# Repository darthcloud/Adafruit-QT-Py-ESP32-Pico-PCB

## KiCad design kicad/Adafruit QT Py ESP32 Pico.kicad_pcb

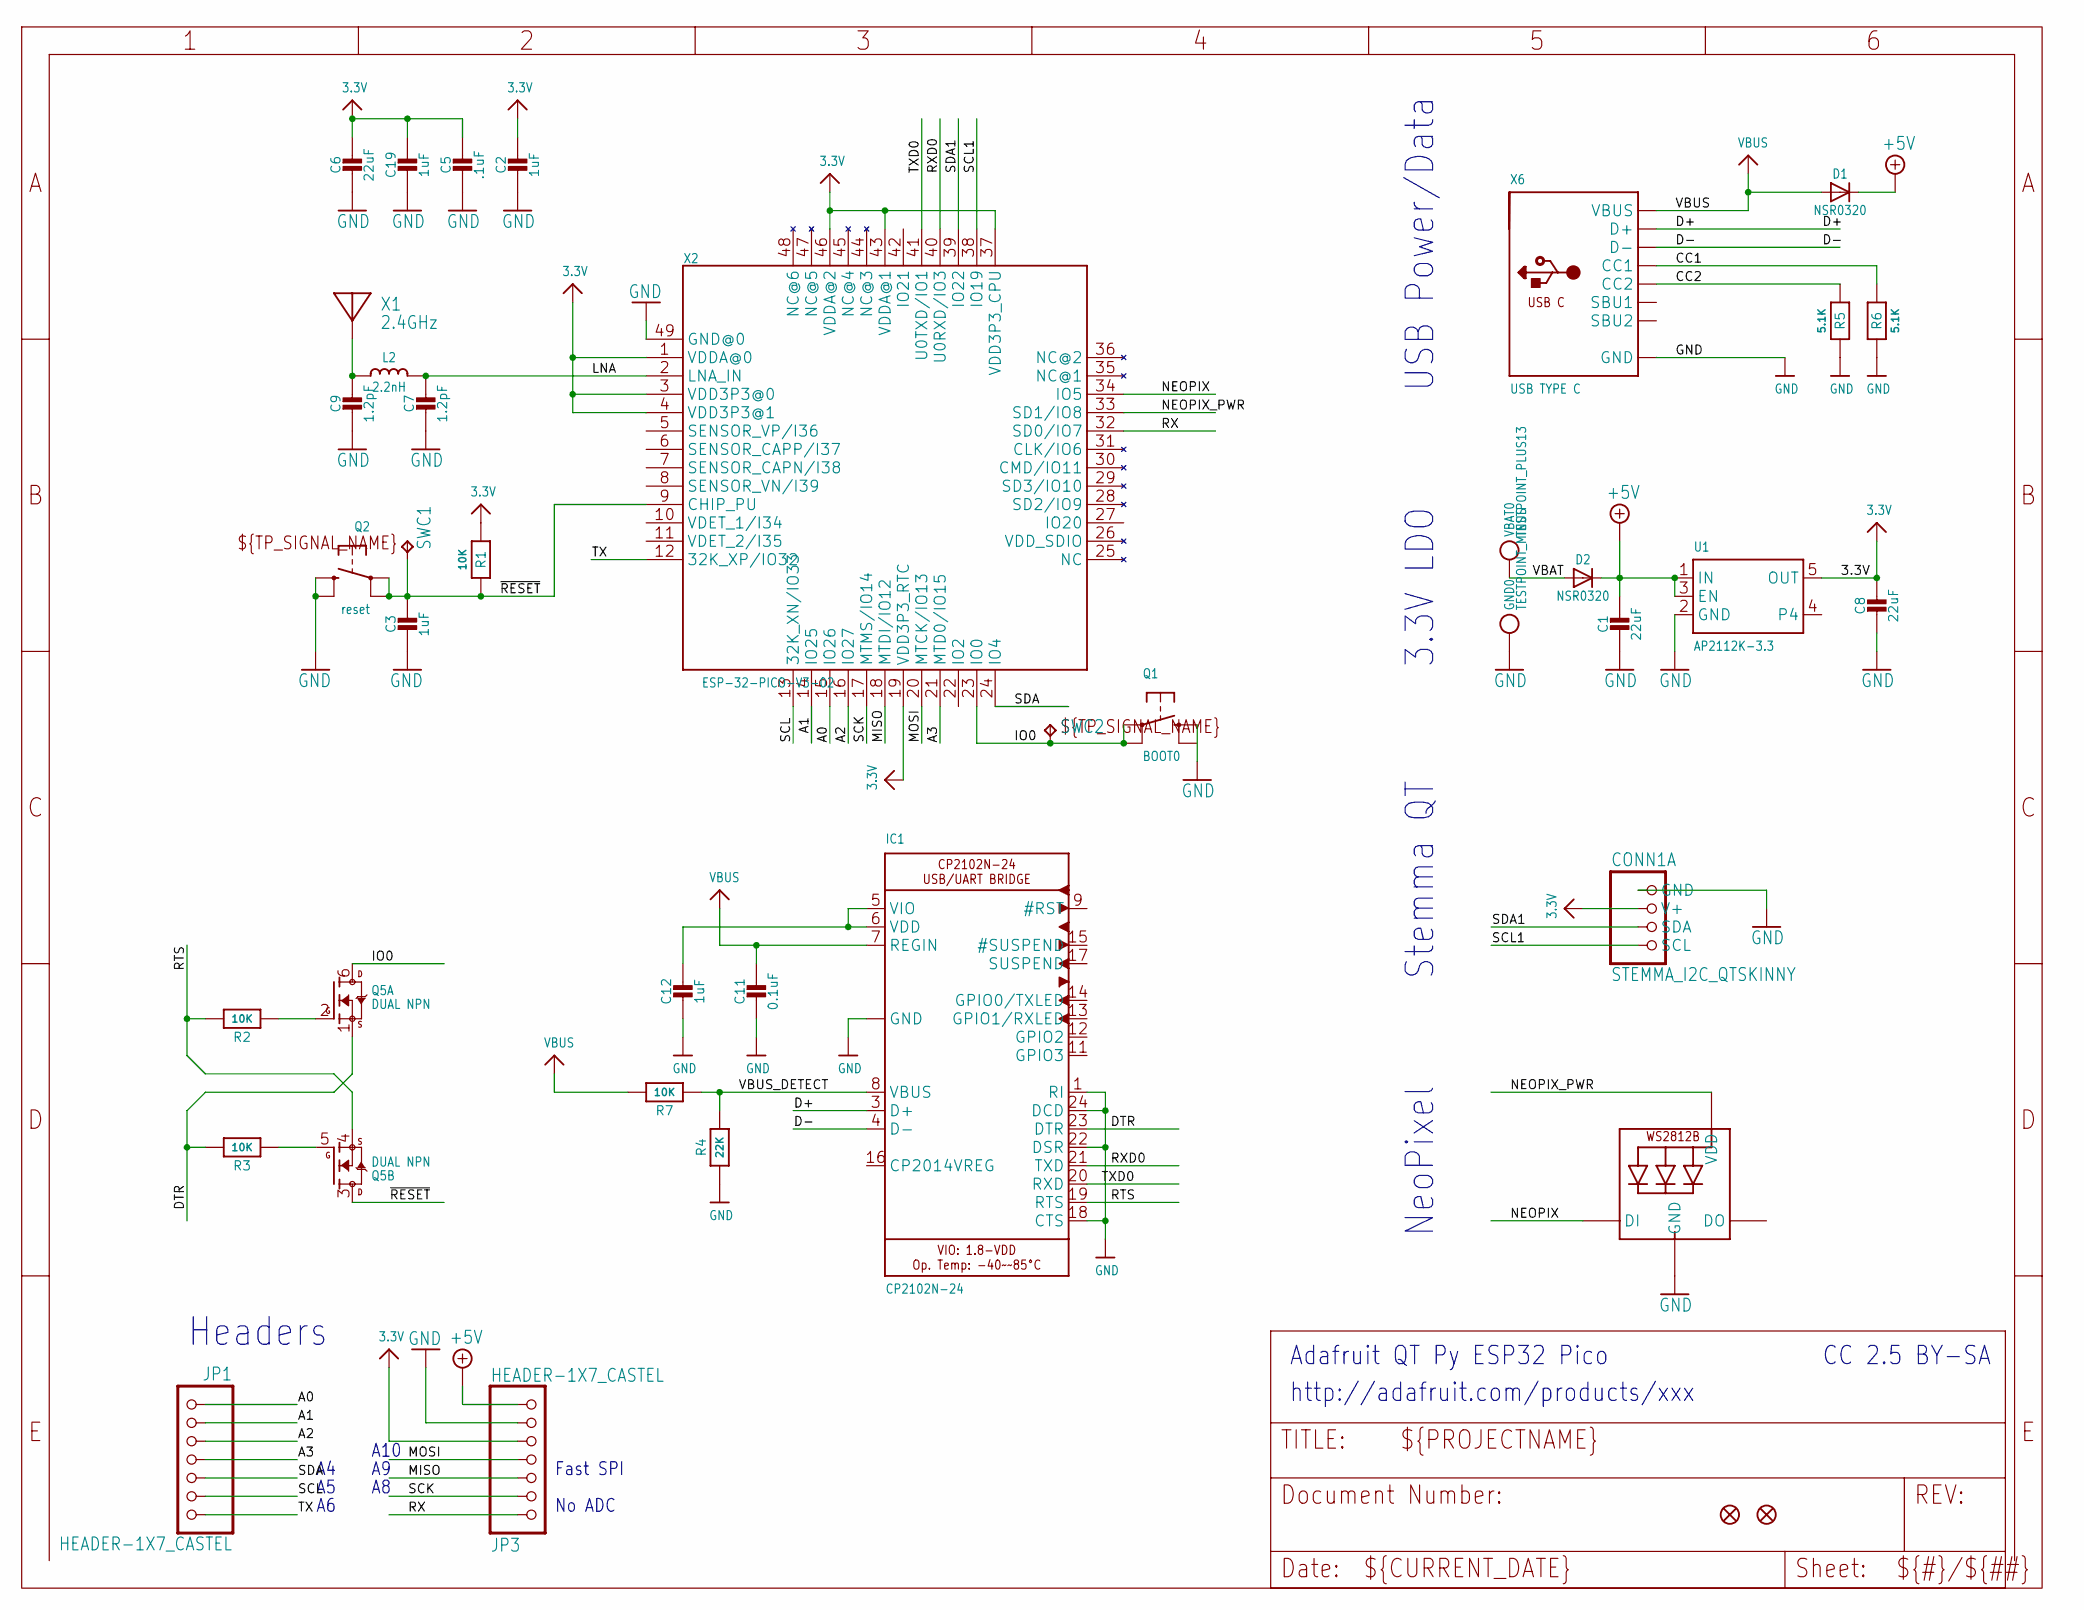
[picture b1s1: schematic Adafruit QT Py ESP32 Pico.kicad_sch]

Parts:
C1, C6, C8: 22uF; 0805-NO
C2, C3, C12: 1uF; _0402NO
C5: .1uF; _0402NO
C7, C9: 1.2pF; _0402NO
C11: 0.1uF; _0402NO
C19: 1uF; 0603-NO_WIDE
CONN1: STEMMA_I2C_QTSKINNY; JST_SH4_SKINNY
D1, D2: NSR0320; SOD-323_MINI
GND0: TESTPOINT_MINUS; TESTPOINT_MINUS_1X3MM
IC1: CP2102N-24; QFN24_4MM_SMSC
JP1, JP3: HEADER-1X7_CASTEL; 1X07_CASTEL
L2: 2.2nH; _0402
LED1: WS2812B_SK6805_1515; SK6805_1515
Q1: BOOT0; BTN_KMR2_4.6X2.8
Q2: reset; BTN_KMR2_4.6X2.8
Q5: DUAL NPN; SOT363
R1, R2, R3, R7: 10K; _0402NO
R4: 22K; _0402NO
R5, R6: 5.1K; _0402NO
SWC1, SWC2: TPB1,27; B1,27
U1: AP2112K-3.3; SOT23-5
U$6, U$8: FIDUCIAL_1MM
VBAT0: TESTPOINT_PLUS13; TESTPOINT_PLUS_1X3MM
X1: 2.4GHz; ANT_2450AT18B100
X2: ESP-32-PICO-V3-02; QFN48_7X7
X6: USB TYPE C; USB_C_CUSB31-CFM2AX-01-X

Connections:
3.3V: C2.1, C5.1, C6.1, C8.1, C19.1, CONN1.2 (V+), JP3.5, JP3.5C (5), R1.1, U1.5 (OUT), X2.1 (VDDA@0), X2.3 (VDD3P3@0), X2.4 (VDD3P3@1), X2.19 (VDD3P3_RTC), X2.37 (VDD3P3_CPU), X2.43 (VDDA@1), X2.46 (VDDA@2)
+5V: C1.1, D1.C, D2.C, JP3.7, JP3.7C (7), U1.1 (IN), U1.3 (EN)
A0: JP1.1, JP1.1C (1), X2.15 (IO26)
A1: JP1.2, JP1.2C (2), X2.14 (IO25)
A2: JP1.3, JP1.3C (3), X2.16 (IO27)
A3: JP1.4, JP1.4C (4), X2.21 (MTD0/IO15)
CC1: R6.2, X6.A5 (CC1)
CC2: R5.2, X6.B5 (CC2)
D+: IC1.3 (D+), X6.A6 (D+), X6.B6 (D+)
D-: IC1.4 (D-), X6.A7 (D-), X6.B7 (D-)
DTR: IC1.23 (DTR), Q5.1 (S), R3.2
GND: C1.2, C2.2, C3.2, C5.2, C6.2, C7.2, C8.2, C9.2, C11.2, C12.2, C19.2, CONN1.1 (GND), GND0.P$1, IC1.1 (RI), IC1.2 (GND), IC1.18 (CTS), IC1.22 (DSR), IC1.24 (DCD), IC1.THERM (GND), JP3.6, JP3.6C (6), LED1.4 (GND), Q1.B (S), Q1.B' (S1), Q2.B (S), Q2.B' (S1), R4.1, R5.1, R6.1, U1.2 (GND), X2.49 (GND@0), X6.A1B12 (GND), X6.B1A12 (GND)
IO0: Q1.A, Q1.A' (P1), Q5.6 (D), SWC2.TP, X2.23 (IO0)
LNA: C7.1, L2.2, X2.2 (LNA_IN)
MISO: JP3.3, JP3.3C (3), X2.18 (MTDI/IO12)
MOSI: JP3.4, JP3.4C (4), X2.20 (MTCK/IO13)
unnamed: C12.1, IC1.5 (VIO), IC1.6 (VDD)
unnamed: C9.1, L2.1, X1.FP
unnamed: Q5.5 (G), R3.1
unnamed: Q5.2 (G), R2.1
NEOPIX: LED1.1 (DI), X2.34 (IO5)
NEOPIX_PWR: LED1.2 (VDD), X2.33 (SD1/IO8)
RTS: IC1.19 (RTS), Q5.4 (S), R2.2
RX: JP3.1, JP3.1C (1), X2.32 (SD0/IO7)
RXD0: IC1.21 (TXD), X2.40 (U0RXD/IO3)
SCK: JP3.2, JP3.2C (2), X2.17 (MTMS/IO14)
SCL: JP1.6, JP1.6C (6), X2.13 (32K_XN/IO33)
SCL1: CONN1.4 (SCL), X2.38 (IO19)
SDA: JP1.5, JP1.5C (5), X2.24 (IO4)
SDA1: CONN1.3 (SDA), X2.39 (IO22)
TX: JP1.7, JP1.7C (7), X2.12 (32K_XP/IO32)
TXD0: IC1.20 (RXD), X2.41 (U0TXD/IO1)
VBAT: D2.A, VBAT0.P$1
VBUS: C11.1, D1.A, IC1.7 (REGIN), R7.2, X6.A4B9 (VBUS), X6.B4A9 (VBUS)
VBUS_DETECT: IC1.8 (VBUS), R4.2, R7.1
~RESET: C3.1, Q2.A, Q2.A' (P1), Q5.3 (D), R1.2, SWC1.TP, X2.9 (CHIP_PU)

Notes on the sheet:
Fast SPI
http://adafruit.com/products/xxx
3.3V LDO
USB Power/Data
No ADC
NeoPixel
A10
Headers
CC 2.5 BY-SA
Stemma QT
Adafruit QT Py ESP32 Pico

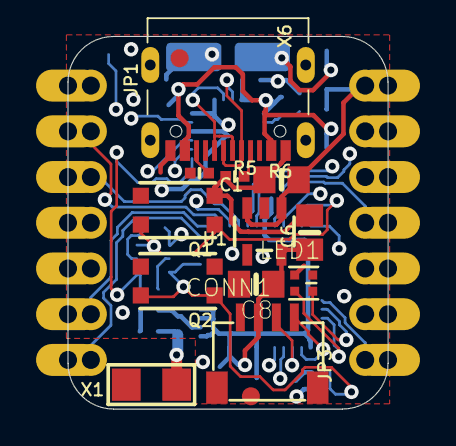
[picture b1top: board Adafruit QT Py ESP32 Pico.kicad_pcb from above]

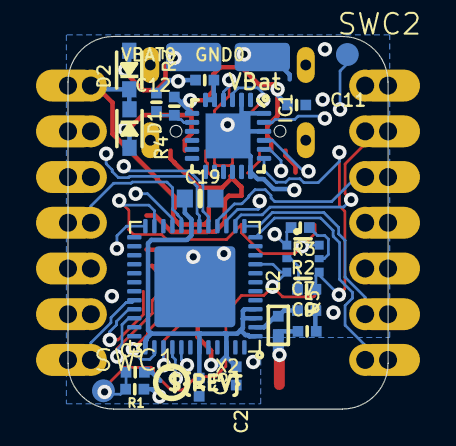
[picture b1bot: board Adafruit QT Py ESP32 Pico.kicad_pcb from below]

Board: 4 copper layers, 17.8 x 20.7 mm, 42 parts (25 on the bottom side), 36 nets.

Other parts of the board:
U$3: QTPY_ESP32_BOT
U$12: PCBFEAT-REV-040
U$22: QTPY_ESP32_TOP

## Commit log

2026-01-30 Kicad 9 auto import
